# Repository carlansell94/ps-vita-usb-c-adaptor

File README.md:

A USB type C board for use with a Vita PCH-1000 (original model) charging connector. A charging connector assembly is required, as this board is designed to fit into the connector housing (trimming required).

Features:
* Includes pads for 5.1k&#937; resistors, to allow the use of 'smart' chargers.
* Compact design limits the board overhang using the original housing.

Included in this repository are the KiCAD files for this design. If you're only interested in having the board manufactured, gerbers are available under 'releases'.

Parts List:
* 1x 16 pin USB type C port
* 2x 0603 5.1k&#937; resistors (optional)
* 1x Vita PCH-1000 charging connector

When having the board manufactured, ensure they offer a 0.8mm board thickness - I used OSH Park for mine.

For more information, take a look at [my blog post](https://qubitsandbytes.co.uk/making-a-ps-vita-usb-c-charger).

## Image
KiCAD render:

## KiCAD
The USB Type C port pictured in the 3D render can be found [over here](https://github.com/ai03-2725/Type-C.pretty) - the file you're looking for is 'HRO TYPE-C-31-M-12.step'. It's not required, unless you want to see the part populated using the 3D viewer.

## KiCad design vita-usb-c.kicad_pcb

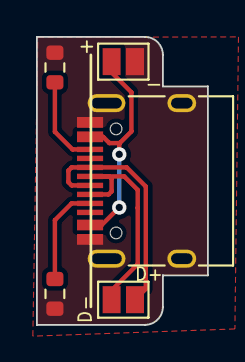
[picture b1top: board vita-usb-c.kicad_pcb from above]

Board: 2 copper layers, 9.5 x 16.0 mm, 5 parts (0 on the bottom side), 6 nets.

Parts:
+: Jack-DC; SolderJumper-2_P1.3mm_Open_Pad1.0x1.5mm
D+: Jack-DC; SolderJumper-2_P1.3mm_Open_Pad1.0x1.5mm
J3: USB_C_Receptacle; USB_C_Receptacle_HRO_TYPE-C-31-M-12
R1, R2: R_Small; R_0603_1608Metric

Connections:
GND: +.1, J3.A1 (GND), J3.A12 (GND), J3.B1 (GND), J3.B12 (GND), J3.S1 (SHIELD), R1.2, R2.2
unnamed: +.2, J3.A4 (VBUS), J3.A9 (VBUS), J3.B4 (VBUS), J3.B9 (VBUS)
unnamed: D+.1, J3.A6 (D+), J3.B6 (D+)
unnamed: D+.2, J3.A7 (D-), J3.B7 (D-)
unnamed: J3.A5 (CC1), R2.1
unnamed: J3.B5 (CC2), R1.1
